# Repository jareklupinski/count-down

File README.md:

# count-down
A clock that counts down until your next meeting

(the photo makes the lights look blurrier than they are in real life, the LED numbers are very crisp to the human eye)

A Heroku App runs a Python script that downloads your Google Calendar and parses out the next appointment timestamp.

The count-down clock connects to the Heroku App and compares the next appoinment timestamp to the current time.

The clock then displays the hours and minutes or minutes and seconds until your next appointment.

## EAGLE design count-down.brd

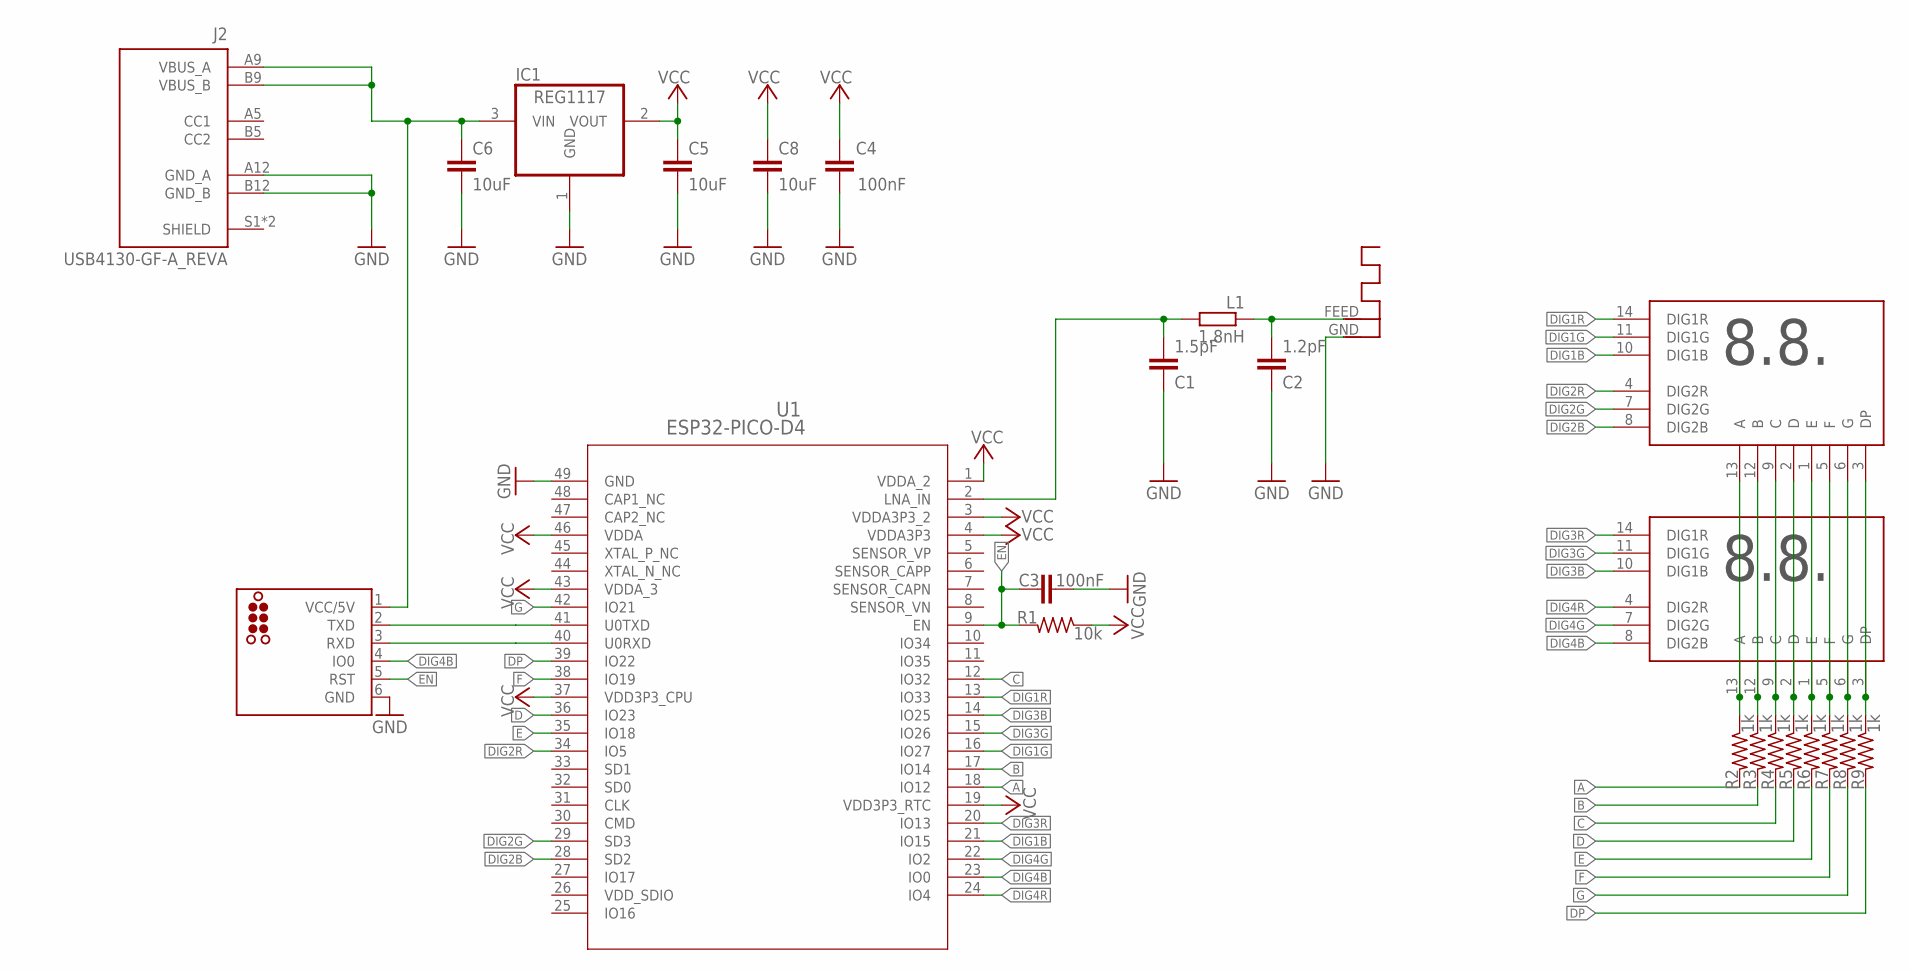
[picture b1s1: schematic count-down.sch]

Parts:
ANT1: ANTENNA; RN-ANT
C1: 1.5pF; C0402
C2: 1.2pF; C0402
C3, C4: 100nF; C0402
C5, C6, C8: 10uF; C0805
IC1: REG1117; SOT223
J2: USB4130-GF-A_REVA; GCT_USB4130-GF-A_REVA
L1: 1.8nH; R0402
LED1, LED2: ACD8143DIP; DIP14
R1: 10k; R0402
R2, R3, R4, R5, R6, R7, R8, R9: 1k; R0402
U1: ESP32-PICO-D4; ESP32-PICO-D4_EXP
U$1: TC2030-ESP; TC2030-MCP

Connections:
A: R2.2, U1.18 (IO12)
B: R3.2, U1.17 (IO14)
C: R4.2, U1.12 (IO32)
D: R5.2, U1.36 (IO23)
DIG1B: LED1.10 (DIG1B), U1.21 (IO15)
DIG1G: LED1.11 (DIG1G), U1.16 (IO27)
DIG1R: LED1.14 (DIG1R), U1.13 (IO33)
DIG2B: LED1.8 (DIG2B), U1.28 (SD2)
DIG2G: LED1.7 (DIG2G), U1.29 (SD3)
DIG2R: LED1.4 (DIG2R), U1.34 (IO5)
DIG3B: LED2.10 (DIG1B), U1.14 (IO25)
DIG3G: LED2.11 (DIG1G), U1.15 (IO26)
DIG3R: LED2.14 (DIG1R), U1.20 (IO13)
DIG4B: LED2.8 (DIG2B), U1.23 (IO0), U$1.4 (IO0)
DIG4G: LED2.7 (DIG2G), U1.22 (IO2)
DIG4R: LED2.4 (DIG2R), U1.24 (IO4)
DP: R9.2, U1.39 (IO22)
E: R6.2, U1.35 (IO18)
EN: C3.2, R1.2, U1.9 (EN), U$1.5 (RST)
F: R7.2, U1.38 (IO19)
G: R8.2, U1.42 (IO21)
GND: ANT1.GND, C1.1, C2.1, C3.1, C4.2, C5.2, C6.2, C8.2, IC1.1 (GND), J2.A12 (GND_A), J2.B12 (GND_B), U1.49 (GND), U$1.6 (GND)
unnamed: ANT1.FEED, C2.2, L1.1
unnamed: C1.2, L1.2, U1.2 (LNA_IN)
unnamed: LED1.13 (A), LED2.13 (A), R2.1
unnamed: LED1.12 (B), LED2.12 (B), R3.1
unnamed: LED1.9 (C), LED2.9 (C), R4.1
unnamed: LED1.2 (D), LED2.2 (D), R5.1
unnamed: LED1.1 (E), LED2.1 (E), R6.1
unnamed: LED1.5 (F), LED2.5 (F), R7.1
unnamed: LED1.6 (G), LED2.6 (G), R8.1
unnamed: LED1.3 (DP), LED2.3 (DP), R9.1
unnamed: C6.1, IC1.3 (VIN), J2.A9 (VBUS_A), J2.B9 (VBUS_B), U$1.1 (VCC/5V)
unnamed: U1.41 (U0TXD), U$1.2 (TXD)
unnamed: U1.40 (U0RXD), U$1.3 (RXD)
VCC: C4.1, C5.1, C8.1, IC1.2 (VOUT), R1.1, U1.1 (VDDA_2), U1.3 (VDDA3P3_2), U1.4 (VDDA3P3), U1.19 (VDD3P3_RTC), U1.37 (VDD3P3_CPU), U1.43 (VDDA_3), U1.46 (VDDA)
VDD_SDIO: U1.26 (VDD_SDIO)

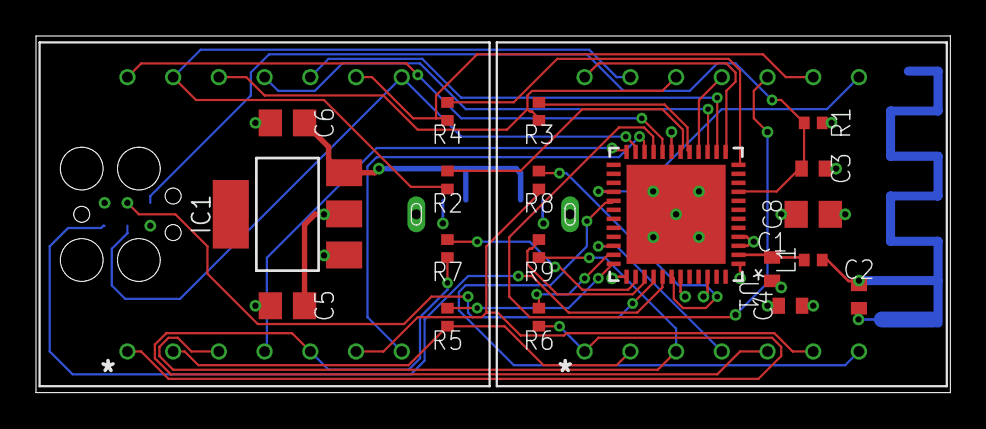
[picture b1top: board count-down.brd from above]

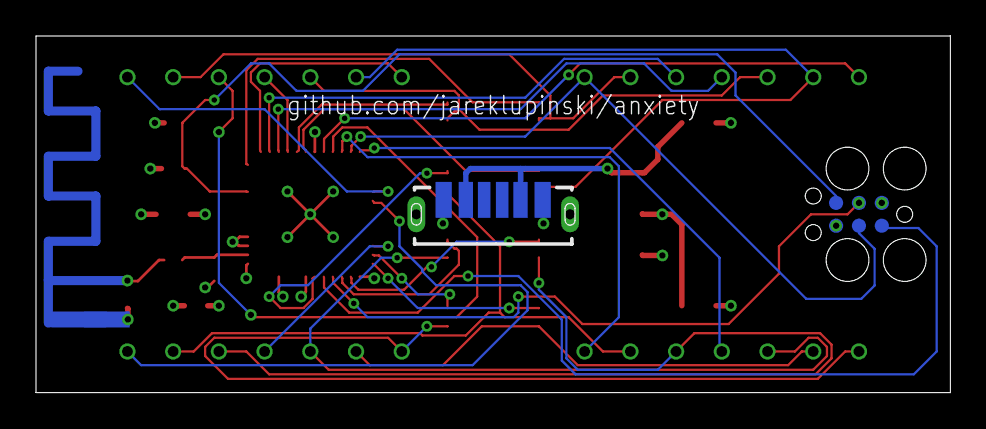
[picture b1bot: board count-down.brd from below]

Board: 4 copper layers, 50.8 x 19.8 mm, 24 parts (3 on the bottom side), 36 nets.

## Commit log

2021-10-24 web app initial commit
2021-10-24 error msg
2021-10-24 dont send fraction
2021-10-27 handle today's repeating events

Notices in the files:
parts and their libraries:
tag-connect: ©2009 ROFA.cz - modified and updated by Robert Darlington ‹rdarlington@gmail.com›
COPYRIGHT: Copyright (C) 2018 Accelerated Designs. All rights reserved
